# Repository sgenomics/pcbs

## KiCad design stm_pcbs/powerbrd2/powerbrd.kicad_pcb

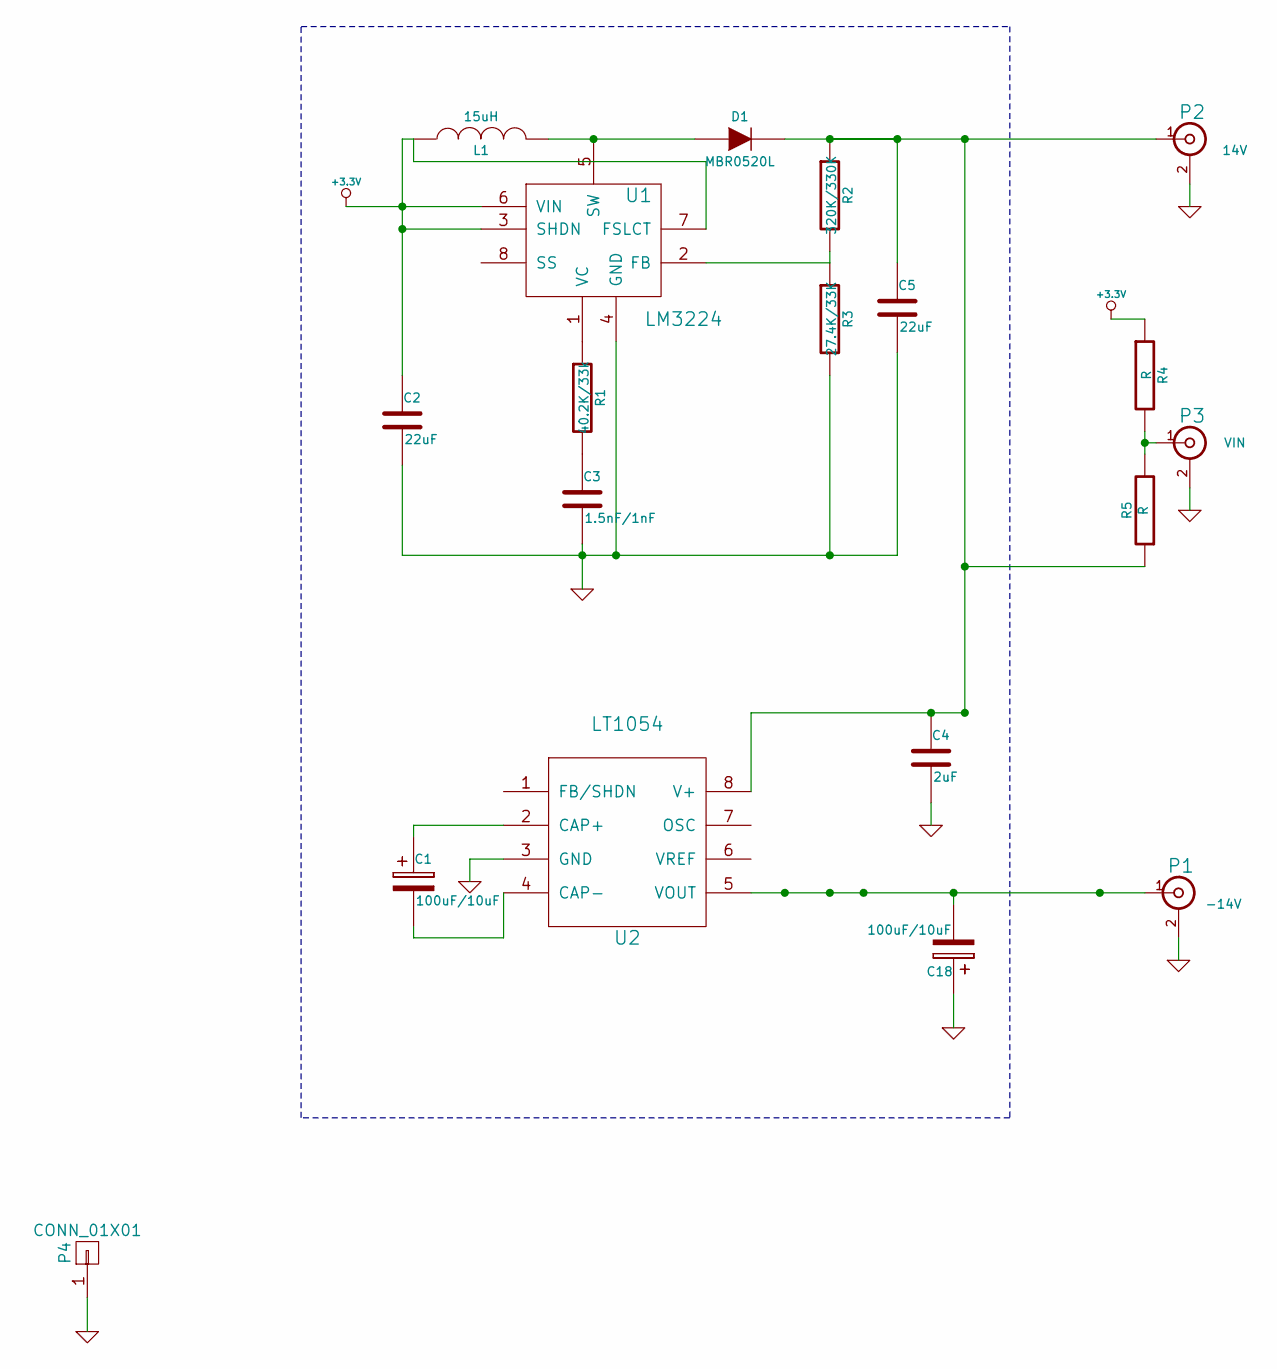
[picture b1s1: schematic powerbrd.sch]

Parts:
C1, C18: 100uF/10uF; c_elec_4x4.5
C2: 22uF; R_1206
C3: 1.5nF/1nF; C_0805
C4: 2uF; SMD-1210_Pol
C5: 22uF; SMD-1210_Pol
D1: MBR0520L; SOD-123
L1: 15uH; INDUCTOR
P1: -14V; SMA
P2: 14V; SMA
P3: VIN; SMA
P4: CONN_01X01; 25x25shield
R1: 40.2K/33k; R_0805_HandSoldering
R2: 320K/330K; R_0805_HandSoldering
R3: 27.4K/33K; R_0805_HandSoldering
R4, R5: R; R_0805_HandSoldering
U1: LM3224; MSOP-8_3x3mm_Pitch0.65mm
U2: LT1054; SOIC-8-N

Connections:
+3.3V: C2.1, L1.1, R4.1, U1.3 (SHDN), U1.6 (VIN), U1.7 (FSLCT)
GND: C2.2, C3.2, C4.2, C5.2, C18.1, P1.2 (Ext), P2.2 (Ext), P3.2 (Ext), P4.1, R3.2, U1.4 (GND), U2.3 (GND)
unnamed: C1.1, U2.2 (CAP+)
unnamed: C1.2, U2.4 (CAP-)
unnamed: C3.1, R1.2
unnamed: C4.1, C5.1, D1.2 (K), P2.1 (In), R2.1, R5.1, U2.8 (V+)
unnamed: C18.2, P1.1 (In), U2.5 (VOUT)
unnamed: D1.1 (A), L1.2, U1.5 (SW)
unnamed: P3.1 (In), R4.2, R5.2
unnamed: R1.1, U1.1 (VC)
unnamed: R2.2, R3.1, U1.2 (FB)

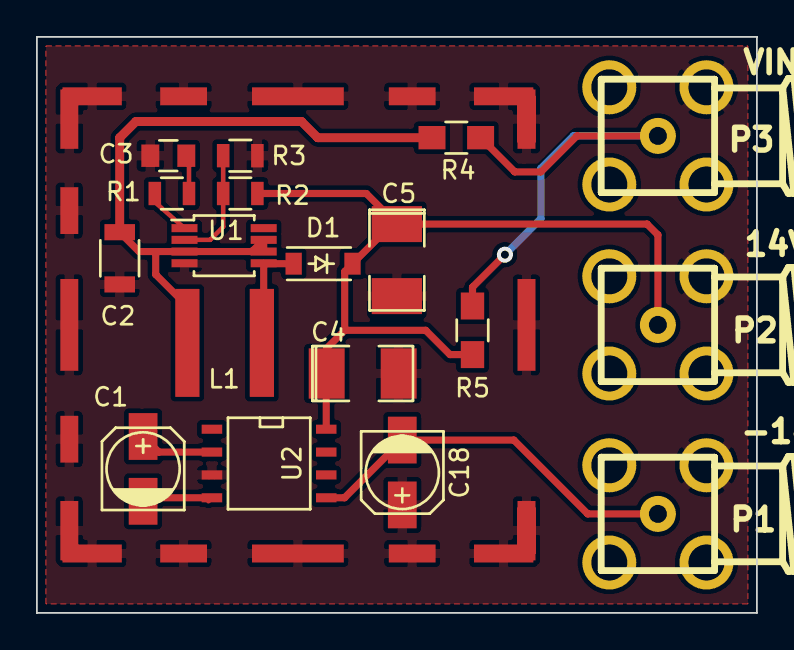
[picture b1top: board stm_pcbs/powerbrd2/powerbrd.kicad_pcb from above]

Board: 2 copper layers, 40.0 x 32.0 mm, 19 parts (0 on the bottom side), 11 nets.

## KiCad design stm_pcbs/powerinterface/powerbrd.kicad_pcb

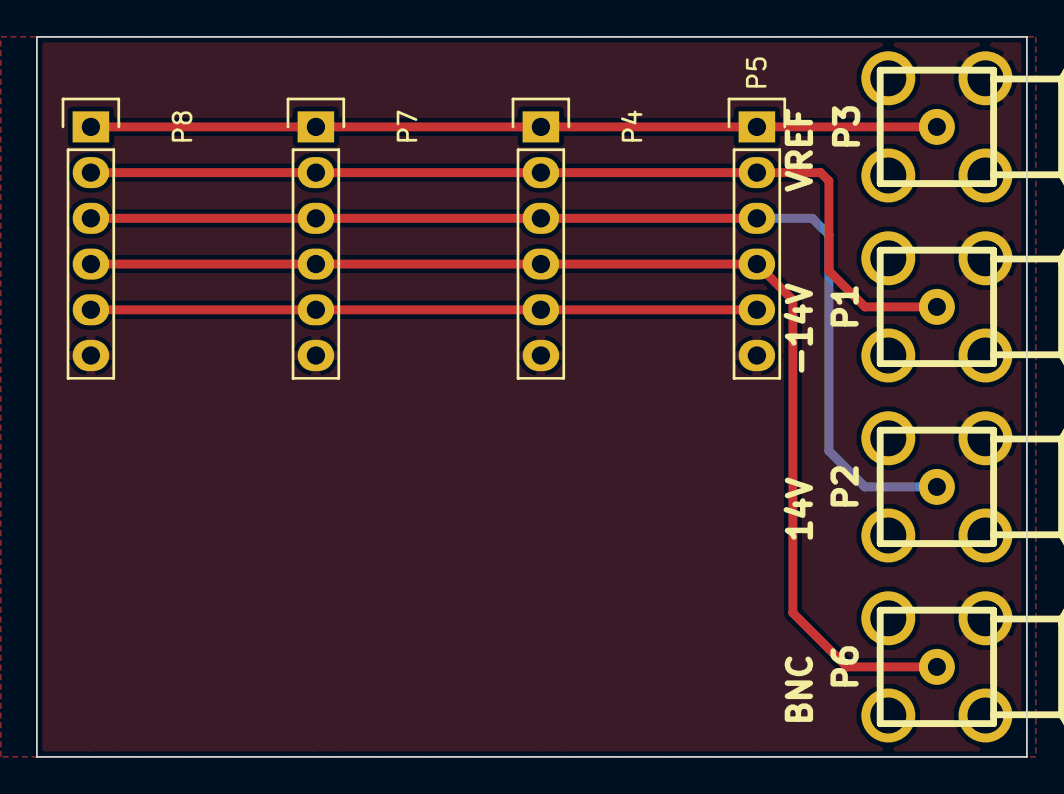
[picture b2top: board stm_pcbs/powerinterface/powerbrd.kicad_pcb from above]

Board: 2 copper layers, 55.0 x 40.0 mm, 8 parts (0 on the bottom side), 6 nets.

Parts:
P1: -14V; SMA
P2: 14V; SMA
P3: VREF; SMA
P4, P5, P7, P8: CONN_01X06; Socket_Strip_Straight_1x06
P6: BNC; SMA

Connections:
GND: P1.2, P2.2, P3.2, P4.6, P5.6, P6.2, P7.6, P8.6
unnamed: P1.1, P4.2, P5.2, P7.2, P8.2
unnamed: P2.1, P4.3, P5.3, P7.3, P8.3
unnamed: P3.1, P4.1, P5.1, P7.1, P8.1
unnamed: P4.4, P5.4, P6.1, P7.4, P8.4
unnamed: P4.5, P5.5, P7.5, P8.5

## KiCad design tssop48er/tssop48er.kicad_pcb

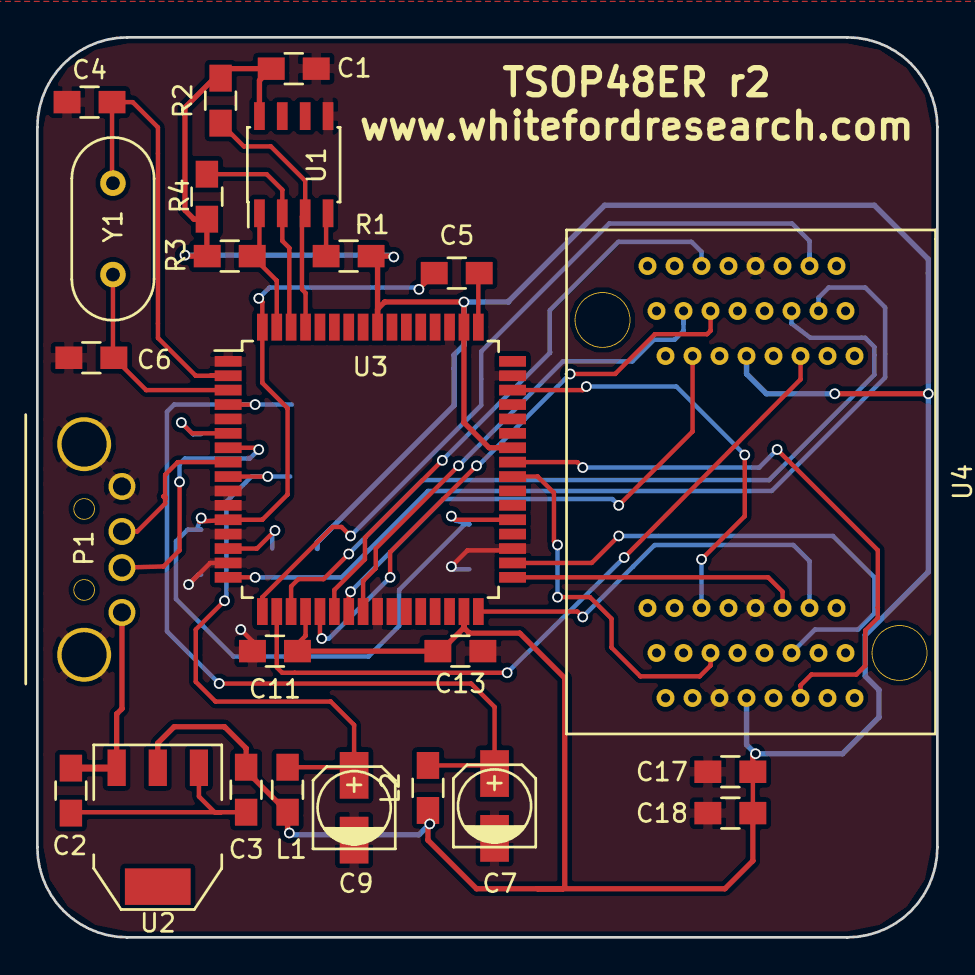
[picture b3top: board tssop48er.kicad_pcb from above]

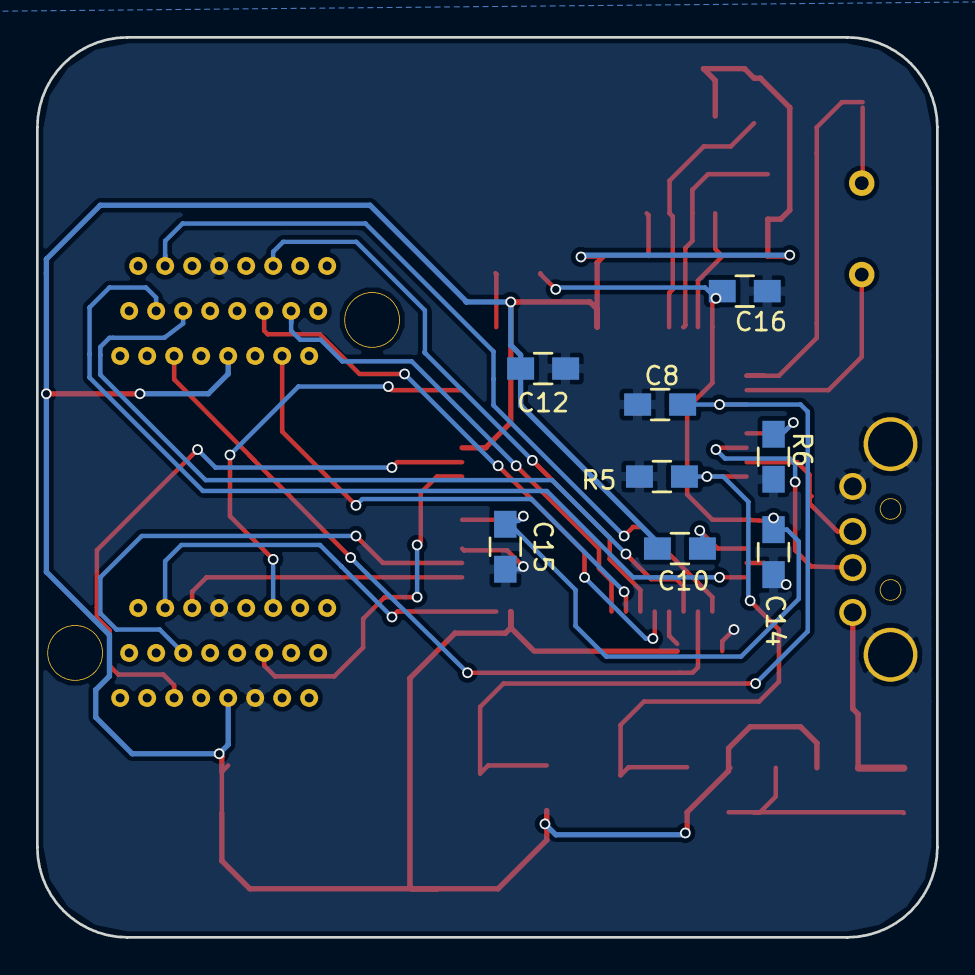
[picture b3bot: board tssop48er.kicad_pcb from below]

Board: 2 copper layers, 50.0 x 50.0 mm, 32 parts (8 on the bottom side), 32 nets.

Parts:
C1, C2, C3, C4, C5, C6, C11, C12, C13, C14, C15, C16, C17, C18: C_Small; C_0805_HandSoldering
C7, C9: 4.7uF; c_elec_4x5.3
C8, C10: 100nF; C_0805_HandSoldering
L1, L2: INDUCTOR_SMALL; C_0805_HandSoldering
P1: USB_B; USB_A
R1, R3, R4, R5: 10K; C_0805_HandSoldering
R2: 2K; C_0805_HandSoldering
R6: 12k; C_0805_HandSoldering
U1: 93CxxA; SOIC-8_3.9x4.9mm_Pitch1.27mm
U2: AP1117; SOT-223
U3: FT2232; LQFP-64_14x14mm_Pitch0.8mm
U4: TSSOP48_NAND; TSOP48ZIF
Y1: Crystal_Small; HC-49V

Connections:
+1V8: C5.1, C14.1, C15.1, C16.1, U3.12, U3.37, U3.64
+3V3: C1.1, C3.1, C11.1, C12.1, C13.1, C17.2, C18.2, L1.1, L2.1, R1.1, R2.2, R3.1, R4.1, R5.1, U1.8, U2.2, U3.20, U3.31, U3.42, U3.50, U3.56, U4.12, U4.37
GND: C1.2, C4.2, C6.2, C7.2, C8.2, C9.2, C10.2, C11.2, C12.2, C13.2, C14.2, C15.2, C16.2, C17.1, C18.1, P1.4, P1.5, R6.1, U1.5, U3.1, U3.5, U3.10, U3.11, U3.13, U3.15, U3.25, U3.35, U3.47, U3.51, U4.9, U4.13, U4.36
NAND_ALE: U3.34, U4.17
NAND_CLE: U3.33, U4.16
NAND_RB: U3.46, U4.7
NAND_RE: U3.40, U4.8
NAND_WE: U3.41, U4.18
NAND_WP: U3.32, U4.19
unnamed: C2.1, P1.1, U2.3
unnamed: C2.2, C3.2, U2.1
unnamed: C4.1, U3.2, Y1.1
unnamed: C5.2, U3.49
unnamed: C6.1, U3.3, Y1.2
unnamed: C7.1, C8.1, L2.2, U3.4
unnamed: C9.1, C10.1, L1.2, U3.9
unnamed: P1.2, U3.7
unnamed: P1.3, U3.8
unnamed: R1.2, U1.4
unnamed: R2.1, U1.3, U3.61
unnamed: R3.2, U1.1, U3.63
unnamed: R4.2, U1.2, U3.62
unnamed: R5.2, U3.14
unnamed: R6.2, U3.6
unnamed: U3.16, U4.29
unnamed: U3.17, U4.30
unnamed: U3.18, U4.31
unnamed: U3.19, U4.32
unnamed: U3.21, U4.41
unnamed: U3.22, U4.42
unnamed: U3.23, U4.43
unnamed: U3.24, U4.44
